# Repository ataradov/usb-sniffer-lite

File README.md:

# Usb Sniffer Lite for RP2040

This is a simple USB sniffer based on a Raspberry Pi RP2040. It supports Low Speed and
Full Speed modes.

The firmware presents itself as a virtual COM-port (VCP), so no additional software
is necessary and it is compatible with all operating systems.

Here are a couple of example capture logs for the [enumeration](doc/usb_fs_enumeration.txt)
and a regular [data transfer](doc/usb_fs_data.txt).

The compiled binary is available [here](bin/UsbSnifferLite.uf2). Boot RP2040 into
the BootROM mode and copy the UF2 file to the drive.

This sniffer has no packet decoding capabilities, but there is an excellent online
[USB Descriptor and Request Parser](https://eleccelerator.com/usbdescreqparser/)
that is very helpful with decoding of the standard descriptors and requests.

The compiled binary needs to have CRC value updated to be recognized by the RP2040.
This can be done using [bin2uf2](https://github.com/ataradov/tools/tree/master/bin2uf2) tool.

## Hardware Connections

USB D+ and D- signals can be directly connected to the MCU pins. The default
pin assignments are shown in the following table:

| RP2040 Pin | Function | USB Cable Color |
|:-------:|:----------------:|:-----:|
| GND     | Ground           | Black |
| GPIO 10 | D+               | Green |
| GPIO 11 | D-               | White |
| GPIO 12 | Start (internal) | N/A   |
| GPIO 18 | Trigger          | N/A   |
| GPIO 25 | Status LED       | N/A   |
| GPIO 26 | Error LED        | N/A   |

The easiest way to connect the signals to the Raspberry Pi Pico board is to splice
the USB cable. It does not have to be pretty. Below is a picture of a cable that
took less than 10 minutes to make. Feel free to make it prettier.

[Here](doc/Hardware.md) are some pictures of a cleaner version based on
the [custom breakout board](https://github.com/ataradov/breakout-boards/tree/master/rp2040).

Trigger input is internally pulled up and the active level is low. When trigger is
enabled in the settings, the capture would pause until the trigger pin is pulled low.
Given the limited size of the capture buffer, trigger mechanism provides a way for
the debugged target to mark the part of interest.

## Dedicated Hardware

There is now a dedicated board. It integrates FE8.1 USB HUB, so you only need one
connection to the host PC. This simplifies setup a lot and eliminates wiring mess
that usually happens when working with USB sniffers.

Normally it is not advised to use the same host port for the sniffer and the target device,
but since in this case only USB Low Speed and Full Speed modes are supported, there
is plenty of bandwidth for both devices.

Schematics and Gerber files are available in the [hardware](hardware/) directory.

## Settings

The following settings are supported:

* Capture speed (e) -- Low / Full
* Capture trigger (g) -- Enabled / Disabled
* Capture limit (l) -- 100/200/500/1000/2000/5000/10000 packets / Unlimited
* Time display format (t) -- Relative to the first packet / previous packet / SOF / bus reset
* Data display format (a) -- Full / Limit to 16 bytes / Limit to 64 bytes / Do not display data
* Fold empty frames (f) -- Enabled / Disabled

A frame is delimited by the SOF packet in the Full Speed mode or by a keep-alive signal in
the Low Speed mode.

An empty frame is a frame that contains no packets other than IN/NAK and contains no packets
with errors detected. Folding of the empty frames shortens the displayed information by
combining consecutive empty frames into one entry, since they don't carry useful information,
but happen very often in a typical USB transaction.

## Commands

The following commands are supported:

* Print the help message (h)
* Display current buffer (b)
* Start capture (s)
* Stop capture (p)

Once capture is started and the trigger condition is met, the sniffer captures the specified
number of packets. After the capture is done, the buffer is displayed using current settings.

The display settings may be adjusted without a new capture. Once the buffer is captured,
it is stored in the memory and can be displayed again using a `b` command.

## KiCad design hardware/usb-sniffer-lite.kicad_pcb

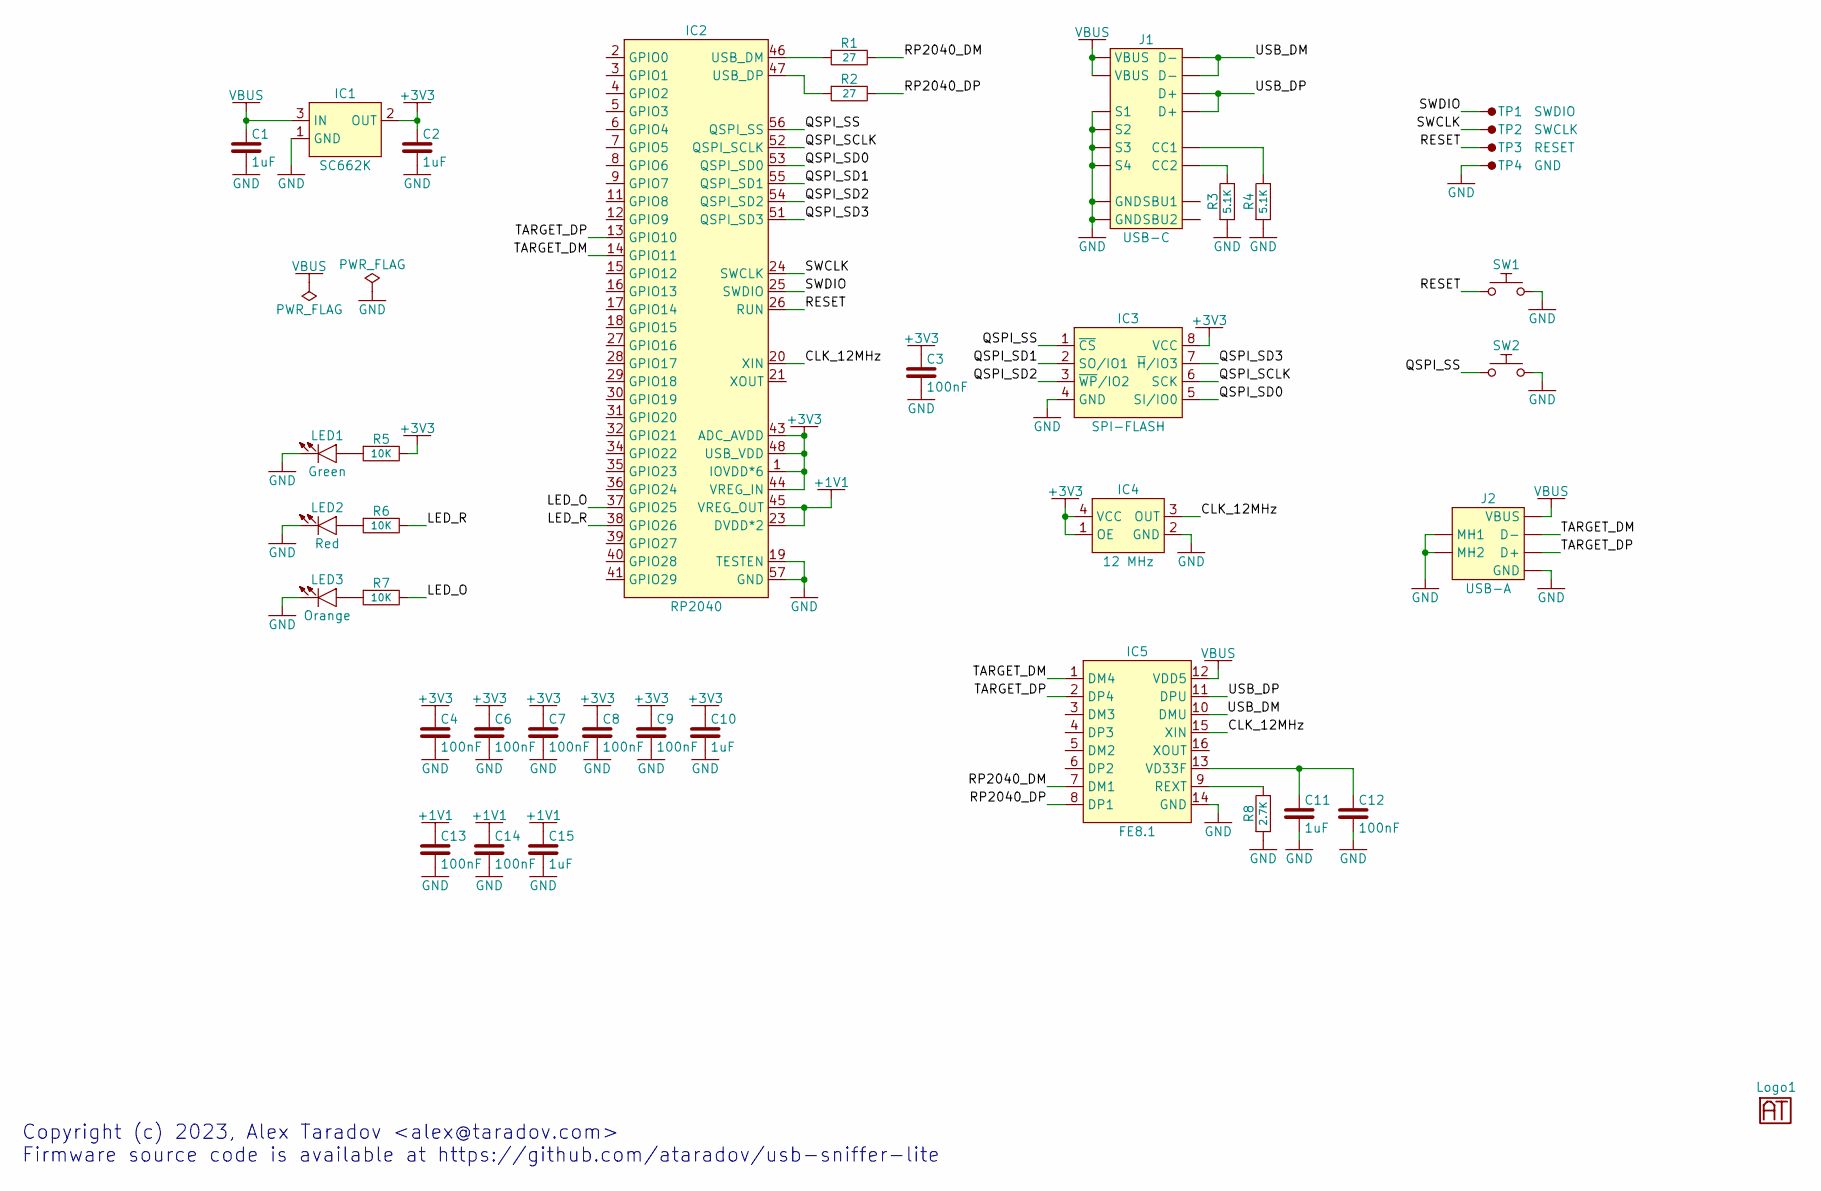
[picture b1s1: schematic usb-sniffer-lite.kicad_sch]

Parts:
C1, C2, C10, C11, C15: 1uF; 0603
C3, C4, C6, C7, C8, C9, C12, C13, C14: 100nF; 0603
IC1: SC662K; SOT-23
IC2: RP2040; QFN-56-0.4mm
IC3: SPI-FLASH; USON-8-3x2mm
IC4: 12 MHz; CDFN-4-3.2x2.5mm
IC5: FE8.1; SSOP-16-0.635mm
J1: USB-C
J2: USB-A; USB-A-Slots
LED1: Green; 0603
LED2: Red; 0603
LED3: Orange; 0603
Logo1: Logo; Logo-Small
R1, R2: 27; 0603
R3, R4: 5.1K; 0603
R5, R6, R7: 10K; 0603
R8: 2.7K; 0603
SW1, SW2: TactSwitch; TactSwitch-6mm-Half-SMD
TP1: SWDIO; TestPoint-1.27mm-Small
TP2: SWCLK; TestPoint-1.27mm-Small
TP3: RESET; TestPoint-1.27mm-Small
TP4: GND; TestPoint-1.27mm-Small

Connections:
+1V1: C13.2, C14.2, C15.2, IC2.23 (DVDD*2), IC2.45 (VREG_OUT), IC2.50 (DVDD*2)
+3V3: C2.2, C3.2, C4.2, C6.2, C7.2, C8.2, C9.2, C10.2, IC1.2 (OUT), IC2.1 (IOVDD*6), IC2.10 (IOVDD*6), IC2.22 (IOVDD*6), IC2.33 (IOVDD*6), IC2.42 (IOVDD*6), IC2.43 (ADC_AVDD), IC2.44 (VREG_IN), IC2.48 (USB_VDD), IC2.49 (IOVDD*6), IC3.8 (VCC), IC4.1 (OE), IC4.4 (VCC), R5.2
/CLK_12MHz: IC2.20 (XIN), IC4.3 (OUT), IC5.15 (XIN)
/LED_O: IC2.37 (GPIO25), R7.2
/LED_R: IC2.38 (GPIO26), R6.2
/QSPI_SCLK: IC2.52 (QSPI_SCLK), IC3.6 (SCK)
/QSPI_SD0: IC2.53 (QSPI_SD0), IC3.5 (SI/IO0)
/QSPI_SD1: IC2.55 (QSPI_SD1), IC3.2 (SO/IO1)
/QSPI_SD2: IC2.54 (QSPI_SD2), IC3.3 (~WP/IO2)
/QSPI_SD3: IC2.51 (QSPI_SD3), IC3.7 (~H/IO3)
/QSPI_SS: IC2.56 (QSPI_SS), IC3.1 (~CS), SW2.1
/RESET: IC2.26 (RUN), SW1.1, TP3.1
/RP2040_DM: IC5.7 (DM1), R1.2
/RP2040_DP: IC5.8 (DP1), R2.2
/SWCLK: IC2.24 (SWCLK), TP2.1
/SWDIO: IC2.25 (SWDIO), TP1.1
/TARGET_DM: IC2.14 (GPIO11), IC5.1 (DM4), J2.D-
/TARGET_DP: IC2.13 (GPIO10), IC5.2 (DP4), J2.D+
/USB_DM: IC5.10 (DMU), J1.D-1 (D-), J1.D-2 (D-)
/USB_DP: IC5.11 (DPU), J1.D+1 (D+), J1.D+2 (D+)
GND: C1.1, C2.1, C3.1, C4.1, C6.1, C7.1, C8.1, C9.1, C10.1, C11.1, C12.1, C13.1, C14.1, C15.1, IC1.1 (GND), IC2.19 (TESTEN), IC2.57 (GND), IC3.4 (GND), IC4.2 (GND), IC5.14 (GND), J1.GND1 (GND), J1.GND2 (GND), J1.S1, J1.S2, J1.S3, J1.S4, J2.GND, J2.MH1, J2.MH2, LED1.2 (K), LED2.2 (K), LED3.2 (K), R3.1, R4.1, R8.1, SW1.2, SW2.2, TP4.1
unnamed: IC2.46 (USB_DM), R1.1
unnamed: IC2.47 (USB_DP), R2.1
unnamed: IC5.9 (REXT), R8.2
unnamed: C11.2, C12.2, IC5.13 (VD33F)
unnamed: J1.CC1, R4.2
unnamed: J1.CC2, R3.2
unnamed: LED1.1 (A), R5.1
unnamed: LED2.1 (A), R6.1
unnamed: LED3.1 (A), R7.1
VBUS: C1.2, IC1.3 (IN), IC5.12 (VDD5), J1.VBUS1 (VBUS), J1.VBUS2 (VBUS), J2.VBUS

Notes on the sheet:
Copyright (c) 2023, Alex Taradov <alex@taradov.com> Firmware source code is available at https://github.com/ataradov/usb-sniffer-lite

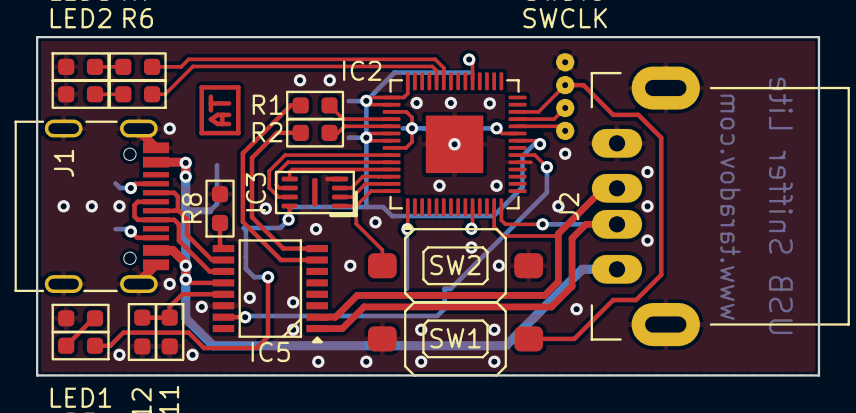
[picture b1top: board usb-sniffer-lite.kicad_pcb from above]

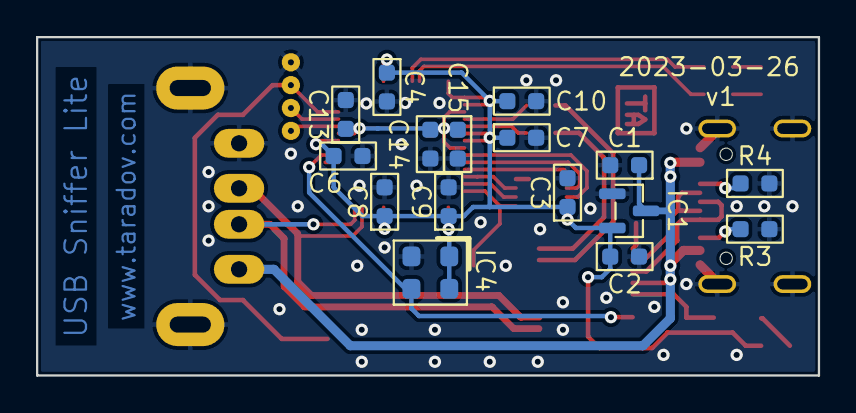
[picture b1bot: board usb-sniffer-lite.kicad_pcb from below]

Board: 2 copper layers, 43.4 x 18.8 mm, 39 parts (16 on the bottom side), 31 nets.

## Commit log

2022-02-16 Initial documentation pass
2022-02-16 Minor fixes
2022-02-16 Added firmware
2022-02-16 Added release binary
2022-02-20 Added custom board pictures
2022-02-20 Moved custom board stuff into a different doc
2022-03-03 Update usb_descriptors.c
    fix the bFirstInterface number in iad
2022-03-03 Updated binat file after the last commit
2022-03-06 Added size display to the data
2022-10-22 Added a link to the descriptor parser
2023-02-23 Added a link to the CRC tool
2023-04-12 Added hardware design files
2023-04-12 More robust handling of the capture start. Should eliminate a lot of bad captures.
2023-04-12 Added custom hardware information
2023-04-15 Added case model and STL files
2024-01-27 Added udev rules
